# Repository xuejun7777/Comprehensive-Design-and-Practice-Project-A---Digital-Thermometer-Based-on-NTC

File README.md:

# NTC数字温度计综合设计项目

## 项目简介

基于STM32G030微控制器和NTC热敏电阻的数字温度计系统，包含完整的硬件设计、软件开发和PCB制作。

## 系统架构

### 硬件组成
- **MCU**: STM32G030 (ARM Cortex-M0+)
- **传感器**: NTC热敏电阻 (10kΩ@25°C, B=3950K)
- **显示**: 4位7段数码管
- **接口**: USB Type-C + UART

### 软件功能
- 12位ADC温度采集
- Steinhart-Hart方程温度转换
- 动态数码管显示
- 串口数据输出
- 开机学号显示

## 核心特性

- **通信**: 115200bps UART

## 项目结构

```
├── g030_adc_uart/          # 主程序代码
├── g030_display/           # 显示驱动
├── NTC/                    # 硬件设计V1
├── NTC2/                   # 硬件设计V2
├── final_submit/           # 最终提交文件
└── *.pdf                   # 实验报告文档
```

## 关键算法

### 温度转换公式
```c
// Steinhart-Hart方程
T = 1/((ln(Rt/R0)/B) + (1/T0)) - 273.15
```

### 自然对数实现
```c
// 泰勒级数展开避免math.h依赖
double tsp_ln(double a) {
    // 15阶泰勒级数计算
}
```

## 编译环境

- **IDE**: Keil MDK-ARM V5.39.0.0
- **编译器**: ArmClang V6.21
- **代码大小**: ~8KB Flash, ~2KB RAM

## 功能验证

✅ 温度测量精度  
✅ 数码管显示  
✅ 串口通信  
✅ 学号显示  
✅ 异常检测  
✅ PCB硬件  

## 应用场景

- 温度监测系统
- 实验室测温设备  
- 工业过程控制
- 教学实验平台

---

*本项目展示了完整的嵌入式系统开发流程，从硬件设计到软件实现的工程实践。*

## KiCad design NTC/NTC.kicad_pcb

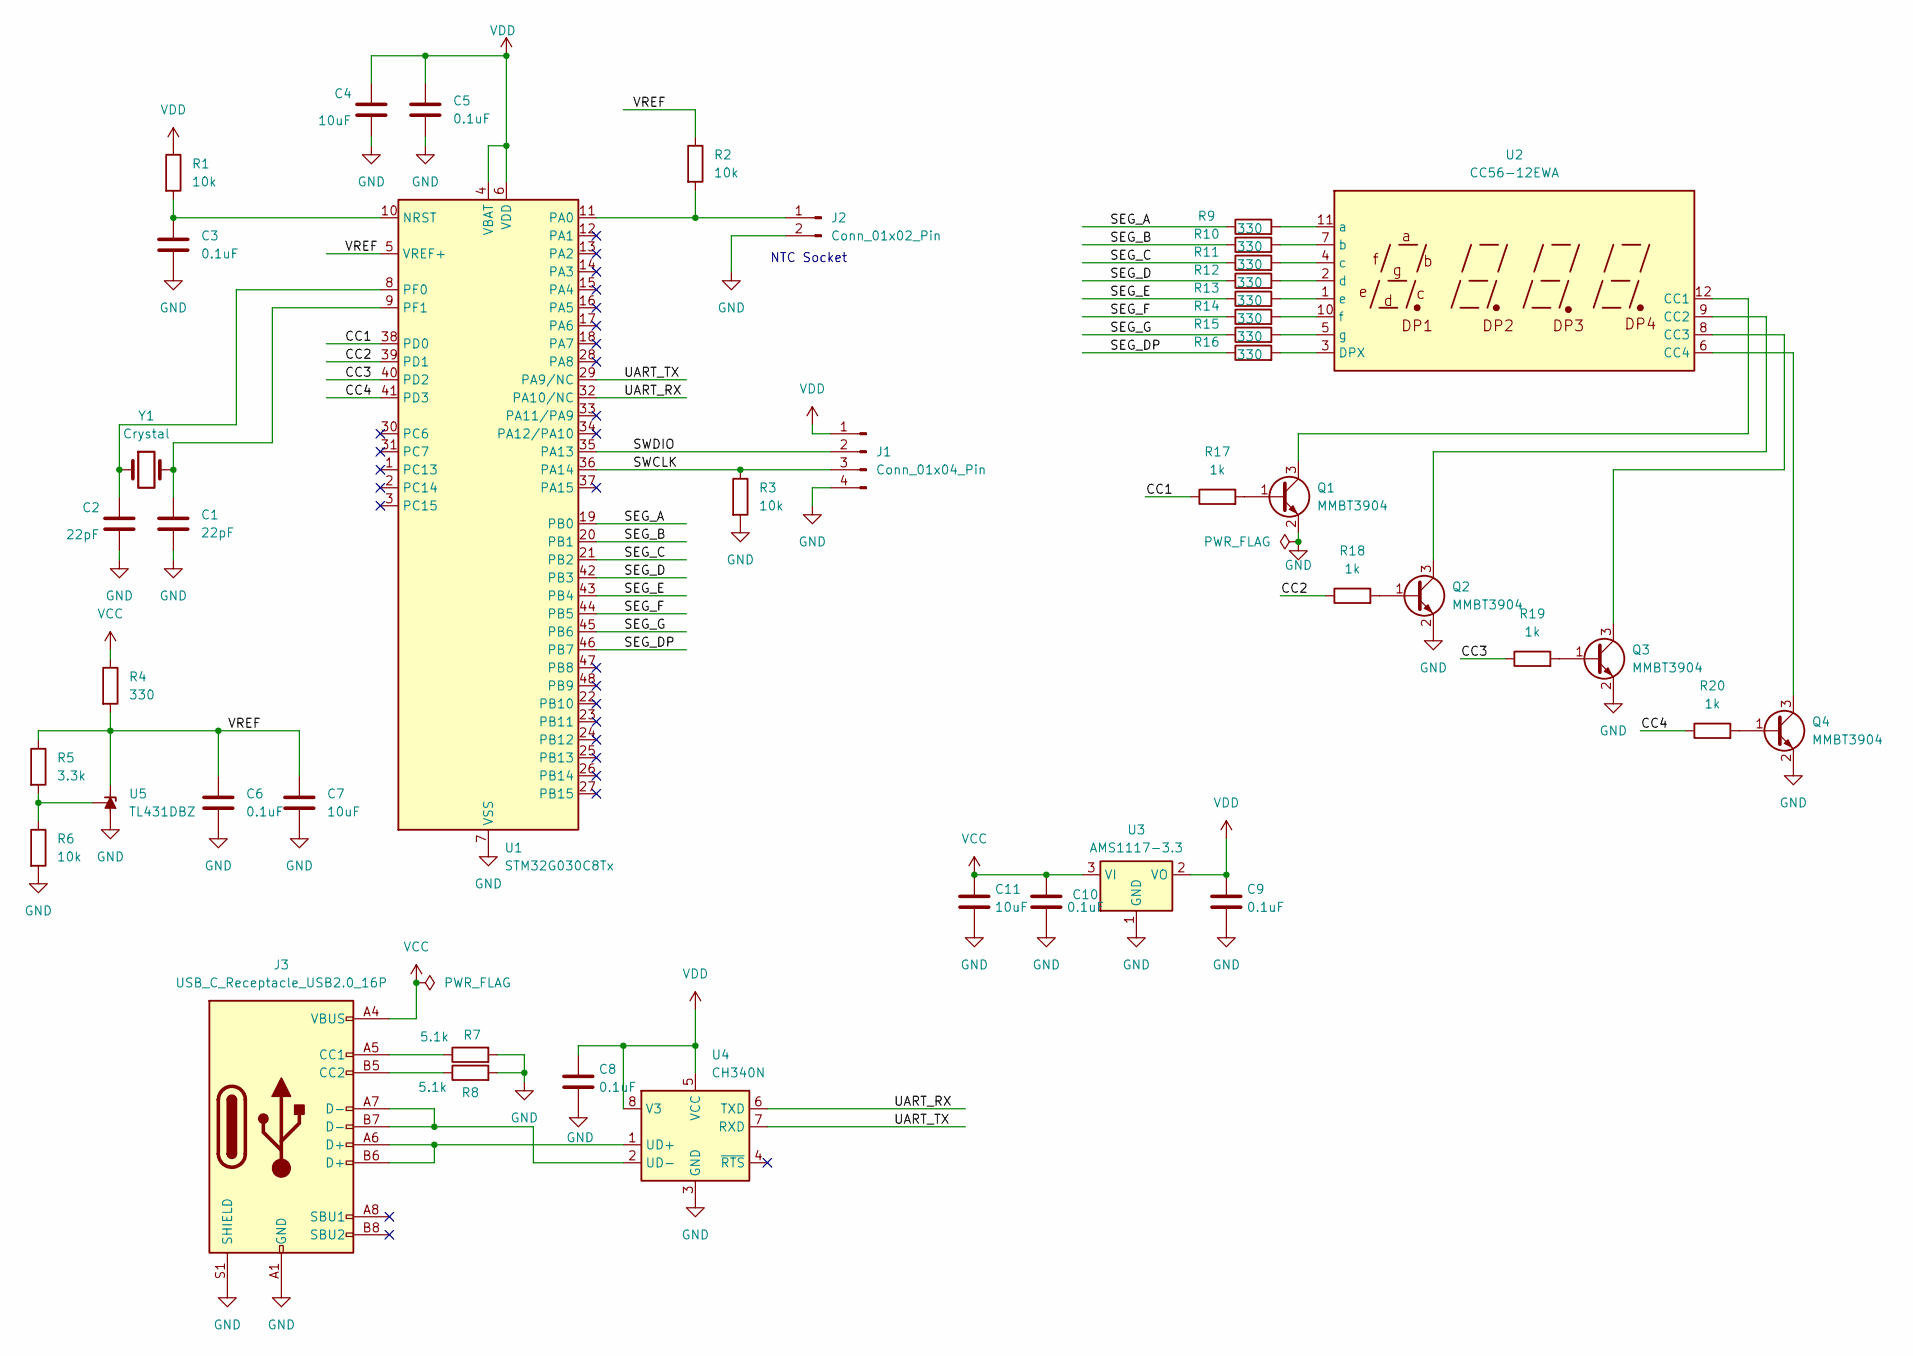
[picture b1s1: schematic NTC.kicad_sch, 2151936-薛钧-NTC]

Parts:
C1, C2: 22pF; C_0805_2012Metric_Pad1.18x1.45mm_HandSolder
C3, C5, C6, C8, C9, C10: 0.1uF; C_0805_2012Metric_Pad1.18x1.45mm_HandSolder
C4, C7, C11: 10uF; C_0805_2012Metric_Pad1.18x1.45mm_HandSolder
J1: Conn_01x04_Pin; PinHeader_1x04_P2.54mm_Vertical
J2: Conn_01x02_Pin; JST_XH_B2B-XH-A_1x02_P2.50mm_Vertical
J3: USB_C_Receptacle_USB2.0_16P; USB_C_Receptacle_HCTL_HC-TYPE-C-16P-01A
Q1, Q2, Q3, Q4: MMBT3904; SOT-23
R1, R2, R3, R6: 10k; R_0805_2012Metric_Pad1.20x1.40mm_HandSolder
R4, R9, R10, R11, R12, R13, R14, R15, R16: 330; R_0805_2012Metric_Pad1.20x1.40mm_HandSolder
R5: 3.3k; R_0805_2012Metric_Pad1.20x1.40mm_HandSolder
R7, R8: 5.1k; R_0805_2012Metric_Pad1.20x1.40mm_HandSolder
R17, R18, R19, R20: 1k; R_0805_2012Metric_Pad1.20x1.40mm_HandSolder
U1: STM32G030C8Tx; LQFP-48_7x7mm_P0.5mm
U2: CC56-12EWA; CA56-12EWA
U3: AMS1117-3.3; SOT-223-3_TabPin2
U4: CH340N; SOIC-8_3.9x4.9mm_P1.27mm
U5: TL431DBZ; SOT-23
Y1: Crystal; Crystal_SMD_5032-2Pin_5.0x3.2mm

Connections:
/CC1: R17.1, U1.38 (PD0)
/CC2: R18.1, U1.39 (PD1)
/CC3: R19.1, U1.40 (PD2)
/CC4: R20.1, U1.41 (PD3)
/SEG_A: R9.1, U1.19 (PB0)
/SEG_B: R10.1, U1.20 (PB1)
/SEG_C: R11.1, U1.21 (PB2)
/SEG_D: R12.1, U1.42 (PB3)
/SEG_DP: R16.1, U1.46 (PB7)
/SEG_E: R13.1, U1.43 (PB4)
/SEG_F: R14.1, U1.44 (PB5)
/SEG_G: R15.1, U1.45 (PB6)
/SWCLK: J1.3, R3.1, U1.36 (PA14)
/SWDIO: J1.2, U1.35 (PA13)
/UART_RX: U1.32 (PA10/NC), U4.6 (TXD)
/UART_TX: U1.29 (PA9/NC), U4.7 (RXD)
/VREF: C6.1, C7.1, R2.1, R4.2, R5.1, U1.5 (VREF+), U5.1 (K)
GND: C1.2, C2.2, C3.2, C4.2, C5.2, C6.2, C7.2, C8.2, C9.2, C10.2, C11.2, J1.4, J2.2, J3.A1 (GND), J3.A12 (GND), J3.B1 (GND), J3.B12 (GND), J3.S1 (SHIELD), Q1.2 (E), Q2.2 (E), Q3.2 (E), Q4.2 (E), R3.2, R6.2, R7.2, R8.2, U1.7 (VSS), U3.1 (GND), U4.3 (GND), U5.3 (A)
unnamed: J2.1, R2.2, U1.11 (PA0)
unnamed: J3.A5 (CC1), R7.1
unnamed: J3.B5 (CC2), R8.1
unnamed: Q1.1 (B), R17.2
unnamed: Q1.3 (C), U2.12 (CC1)
unnamed: Q2.1 (B), R18.2
unnamed: Q2.3 (C), U2.9 (CC2)
unnamed: Q3.1 (B), R19.2
unnamed: Q3.3 (C), U2.8 (CC3)
unnamed: Q4.1 (B), R20.2
unnamed: Q4.3 (C), U2.6 (CC4)
unnamed: C3.1, R1.2, U1.10 (NRST)
unnamed: C2.1, U1.8 (PF0), Y1.1
unnamed: C1.1, U1.9 (PF1), Y1.2
unnamed: R16.2, U2.3 (DPX)
unnamed: R9.2, U2.11 (a)
unnamed: R10.2, U2.7 (b)
unnamed: R11.2, U2.4 (c)
unnamed: R12.2, U2.2 (d)
unnamed: R13.2, U2.1 (e)
unnamed: R14.2, U2.10 (f)
unnamed: R15.2, U2.5 (g)
unnamed: J3.A6 (D+), J3.B6 (D+), U4.1 (UD+)
unnamed: J3.A7 (D-), J3.B7 (D-), U4.2 (UD-)
unnamed: R5.2, R6.1, U5.2 (REF)
VCC: C10.1, C11.1, J3.A4 (VBUS), J3.A9 (VBUS), J3.B4 (VBUS), J3.B9 (VBUS), R4.1, U3.3 (VI)
VDD: C4.1, C5.1, C8.1, C9.1, J1.1, R1.1, U1.4 (VBAT), U1.6 (VDD), U3.2 (VO), U4.5 (VCC), U4.8 (V3)

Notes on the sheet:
NTC Socket

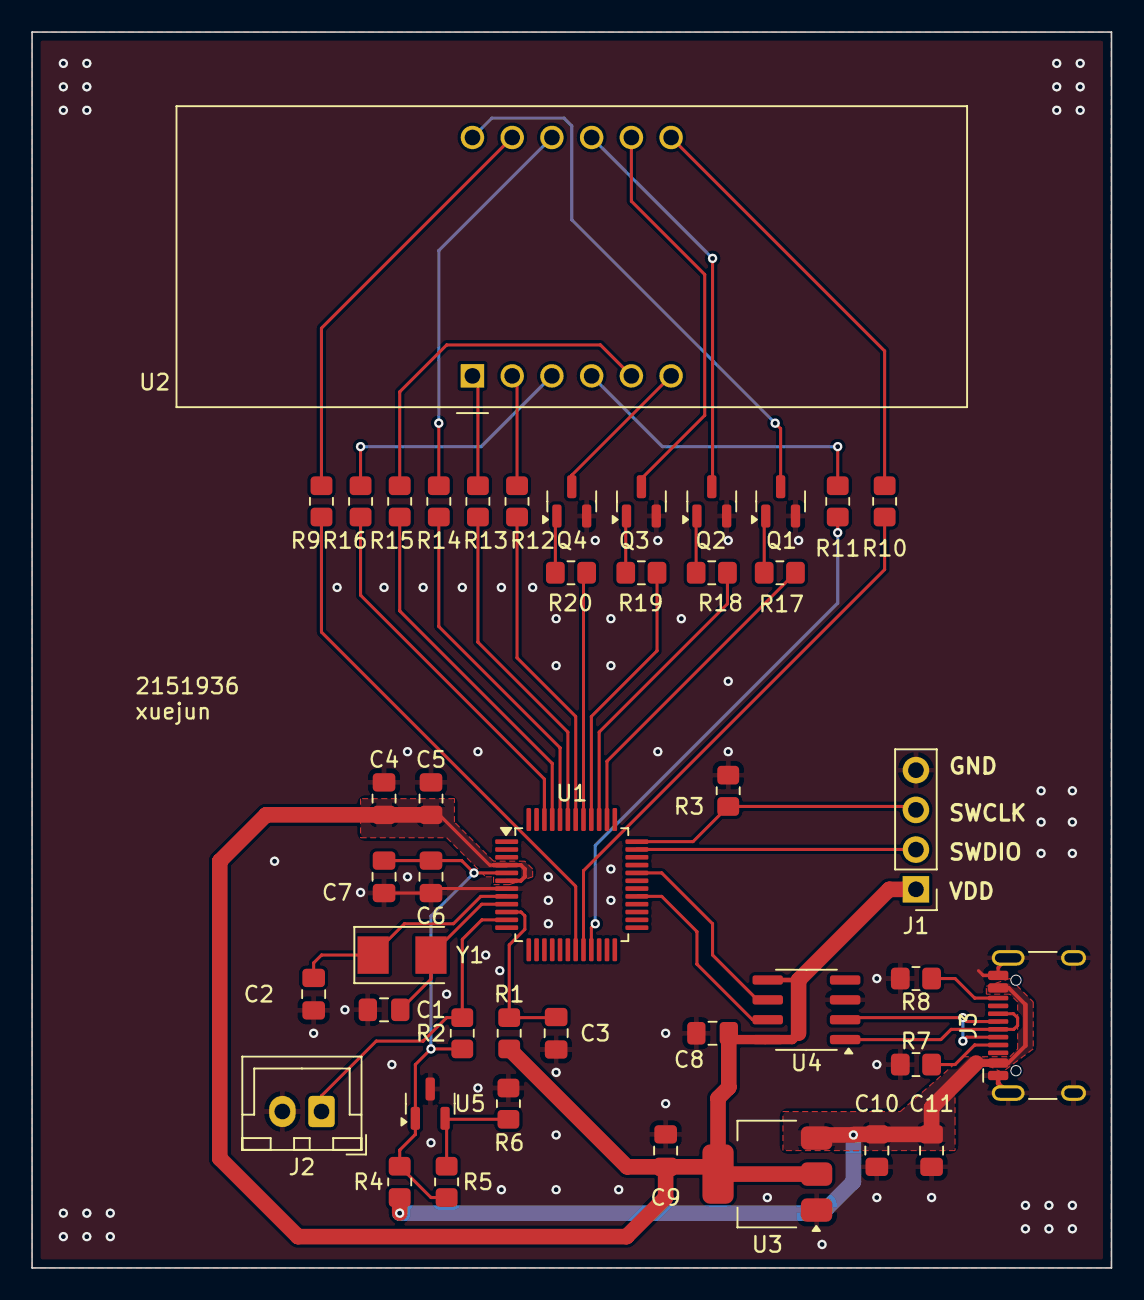
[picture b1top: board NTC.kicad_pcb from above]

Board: 2 copper layers, 69.0 x 79.0 mm, 44 parts (0 on the bottom side), 45 nets.

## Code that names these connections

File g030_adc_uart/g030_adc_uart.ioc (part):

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Mcu.Name=STM32G030C(6-8)Tx
Mcu.Package=LQFP48
Mcu.UserName=STM32G030C8Tx
PA0.Mode=IN0
PA0.Signal=ADC1_IN0
PA10.Mode=Asynchronous
PA10.Signal=USART1_RX
PA13.Mode=Serial_Wire
PA13.Signal=SYS_SWDIO
PA14-BOOT0.Mode=Serial_Wire
PA14-BOOT0.Signal=SYS_SWCLK
PA9.Mode=Asynchronous
PA9.Signal=USART1_TX
PB0.GPIOParameters=GPIO_Label
PB0.GPIO_Label=LED_A
PB0.Signal=GPIO_Output
PB1.GPIOParameters=GPIO_Label
PB1.GPIO_Label=LED_B
PB1.Signal=GPIO_Output
PB2.GPIOParameters=GPIO_Label
PB2.GPIO_Label=LED_C
PB2.Signal=GPIO_Output
PB3.GPIOParameters=GPIO_Label
PB3.GPIO_Label=LED_D
PB3.Signal=GPIO_Output
PB4.GPIOParameters=GPIO_Label
PB4.GPIO_Label=LED_E
PB4.Signal=GPIO_Output
PB5.GPIOParameters=GPIO_Label
PB5.GPIO_Label=LED_F
PB5.Signal=GPIO_Output
PB6.GPIOParameters=GPIO_Label
PB6.GPIO_Label=LED_G
PB6.Signal=GPIO_Output
PB7.GPIOParameters=GPIO_Label
PB7.GPIO_Label=LED_DP
PB7.Signal=GPIO_Output
PD0.GPIOParameters=PinState,GPIO_Label
PD0.GPIO_Label=LED_CC0
PD0.PinState=GPIO_PIN_RESET
PD0.Signal=GPIO_Output
PD1.GPIOParameters=PinState,GPIO_Label
PD1.GPIO_Label=LED_CC1
PD1.PinState=GPIO_PIN_RESET
PD1.Signal=GPIO_Output
PD2.GPIOParameters=PinState,GPIO_Label
PD2.GPIO_Label=LED_CC2
PD2.PinState=GPIO_PIN_RESET
PD2.Signal=GPIO_Output
PD3.GPIOParameters=PinState,GPIO_Label
PD3.GPIO_Label=LED_CC3
PD3.PinState=GPIO_PIN_RESET
PD3.Signal=GPIO_Output
RCC.HSE_VALUE=8000000
RCC.SYSCLKFreq_VALUE=64000000
RCC.SYSCLKSource=RCC_SYSCLKSOURCE_PLLCLK
board=custom

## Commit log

2025-06-18 NTC 温度计所有资料
2025-06-18 add readme
2025-06-18 fix readme
